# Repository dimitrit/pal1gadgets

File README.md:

# PAL1-GADGETS: A range of Gadgets for the PAL-1

The PAL-1 RIOT Expansion Module adds two bidirectional 8-bit digital input/output ports and a programmable interval timer to the PAL-1 system by means of a MOS6532 RAM-I/O-Timer (RIOT) IC.[^1]

This repository includes a number of `gadgets' that can be plugged in to the RIOT Expansion Module to provide specific functionality, including:

  * a [Real-Time Clock](../../tree/master/rtc)
  * a [Speech Processor](../../tree/master/speech)
  * an [Analog-to-Digital Converter](../../tree/master/adc)
  * an [IEC interface](../../tree/master/iec)

Refer to the relevant directories for details on each gadget.

Gadgets are plugged in to the PAL-1 RIOT Expansion Module using a [RIOT adapter](../../tree/master/adapter).

## Example code
Code examples are provided for most gadgets. These code examples use  `vasm6502_oldstyle` syntax[^2] and can be built using `make`.[^3]

## Acknowledgements
PAL-1 and the PAL-1 logo used with kind permission by Liu Ganning.

[^1]: Ganning, Liu, _‘RIOT EXPANSION’_, 2021 <http://pal.aibs.ws/assets/RIOT_expansion_manual.pdf> [accessed 26 January 2024].
[^2]: Barthelmann, Volker and Wille, Frank, `vasm assembler system' (2024), <http://sun.hasenbraten.de/vasm/daily/vasm.tar.gz> [accessed 27 March 2024].
[^3]: Free Software Foundation, `Make - GNU Project', <https://www.gnu.org/
software/make/> [accessed 27 March 2024].

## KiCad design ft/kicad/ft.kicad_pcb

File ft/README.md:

# PAL1-ft: An adapter for the fischertechnik Computing Interface

From the mid 1980s to the early 1990s fischertechnik released a number of construction sets that could be controlled by home computers.[^1] The connection between motors, sensors and the computer was by means of a dedicated Computing Interface.[^2] Different versions of the fischertechnik Computing Interface supported a range of platforms, including Amstrad, Apple, Atari and Commodore. In addition to these dedicated interfaces, fischertechnik also released universal interfaces. The fischertechnik Universal and CVK Computing Interfaces required adapters between the interface connector and target computer systems.

 PAL1-ft is a simple adapter that allows the fischertechnik Universal and CVK Computing Interfaces to be connected to the PAL-1 RIOT Expansion Module.[^3]

The PAL1-ft adapter implements mostly the same logical connections as the fischertechnik Commodore 64 adapter, with the exception of the analog data input:[^4]

| PAL1 RIOT | ft Interface | Description |
| :-------: | :----------: | :---------- |
| PB0       | LOAD_OUT     | Signal digital output |
| PB1       | LOAD_IN      | Signal digital input |
| PB2       | DATA_OUT     | Digital data output  stream |
| PB3       | CLOCK        | Data transfer clock |
| PB4       | TRIGGER_X    | Trigger analog input X |
| PB5       | TRIGGER_Y    | Trigger analog input Y |
| PB7       | DATA_IN<sup>*</sup>      | Digital data input stream |
| PA7       | COUNT_IN     | Analog data input pulses |

<sup>*</sup>The source of DATA_IN is determined by the Data Input Select Jumper. See documentation for details. 

Since the 6532 RIOT timer does not support a pulsed count down mode, the adapter instead routes the analog input to PA7, thereby enabling the use of the RIOT's edge sense interrupt feature. Alternatively, it is possible to measure analog inputs by calculating the time DATA_IN remains LOW after triggering an analog input. For this it is necessary to move the Data Input Select jumper to the CENTRONICS position.

[^1]: fischertechnik, _‘Robots, Automats and graphic units to build yourself’_, 1985, <https://docs.fischertechnikclub.nl/info2/1985.pdf> [accessed 1 September 2025]
[^2]: fischertechnik, _‘Computing Interface’_, N.D., <https://docs.fischertechnikclub.nl/computing/39484.pdf> [accessed 30 August 2025].
[^3]: Liu Ganning, _‘RIOT EXPANSION’_, 2021, <http://pal.aibs.ws/assets/RIOT_expansion_manual.pdf> [accessed 26 January 2024].
[^4]: R Trapp, _‘ft66843 Schematic’_, 2017, <https://ftcommunity.de/knowhow/computing/computing_interfaces/ft66843_schematic.pdf> [accessed 30 August 2025].

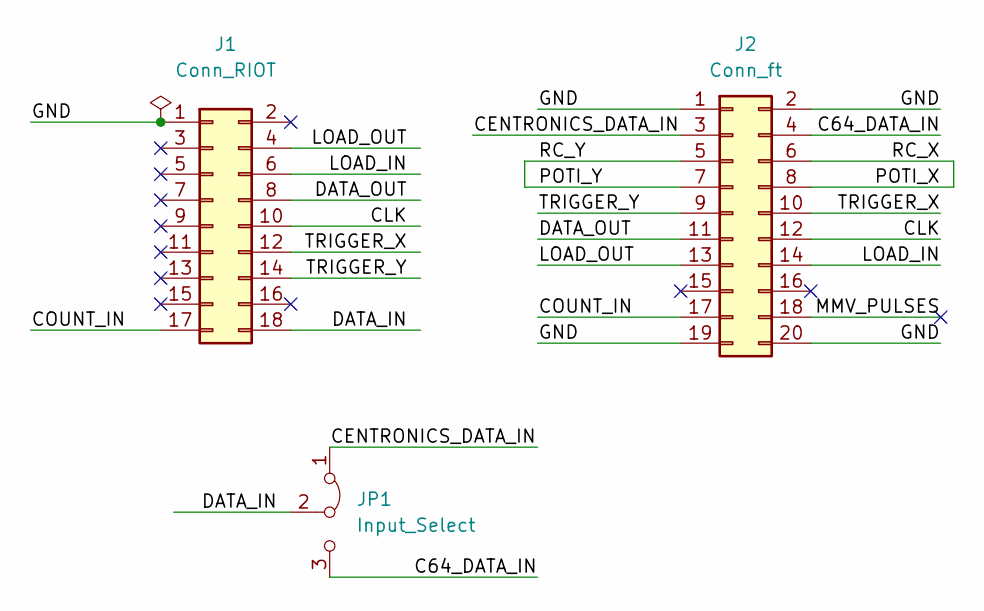
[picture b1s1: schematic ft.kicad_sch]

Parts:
J1: Conn_RIOT; PinSocket_2x09_P2.54mm_Horizontal
J2: Conn_ft; IDC-Header_2x10_P2.54mm_Horizontal
JP1: Input_Select; PinHeader_1x03_P2.54mm_Vertical

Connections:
/C64_DATA_IN: J2.4, JP1.3 (B)
/CENTRONICS_DATA_IN: J2.3, JP1.1 (A)
/CLK: J1.10, J2.12
/COUNT_IN: J1.17, J2.17
/DATA_IN: J1.18, JP1.2 (C)
/DATA_OUT: J1.8, J2.11
/GND: J1.1, J2.1, J2.2, J2.19, J2.20
/LOAD_IN: J1.6, J2.14
/LOAD_OUT: J1.4, J2.13
/MMV_PULSES: J2.18
/POTI_X: J2.6, J2.8
/POTI_Y: J2.5, J2.7
/TRIGGER_X: J1.12, J2.10
/TRIGGER_Y: J1.14, J2.9

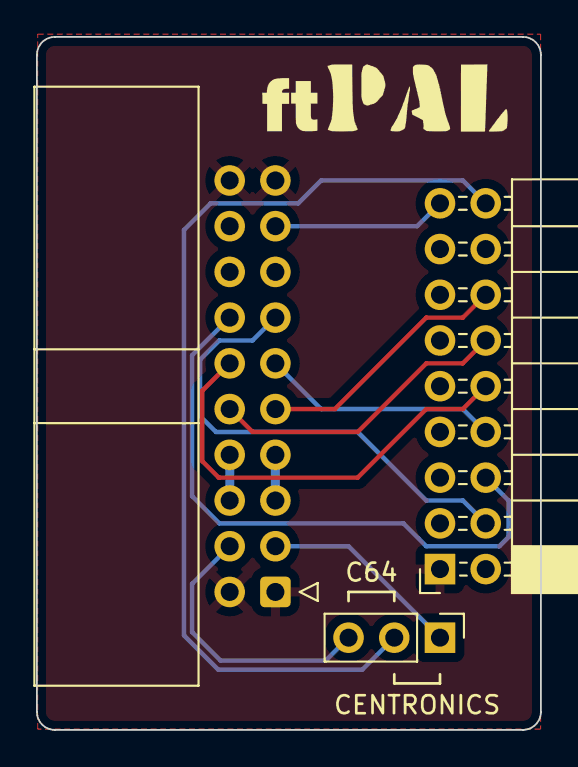
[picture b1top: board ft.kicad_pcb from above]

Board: 2 copper layers, 28.0 x 38.5 mm, 3 parts (0 on the bottom side), 13 nets.

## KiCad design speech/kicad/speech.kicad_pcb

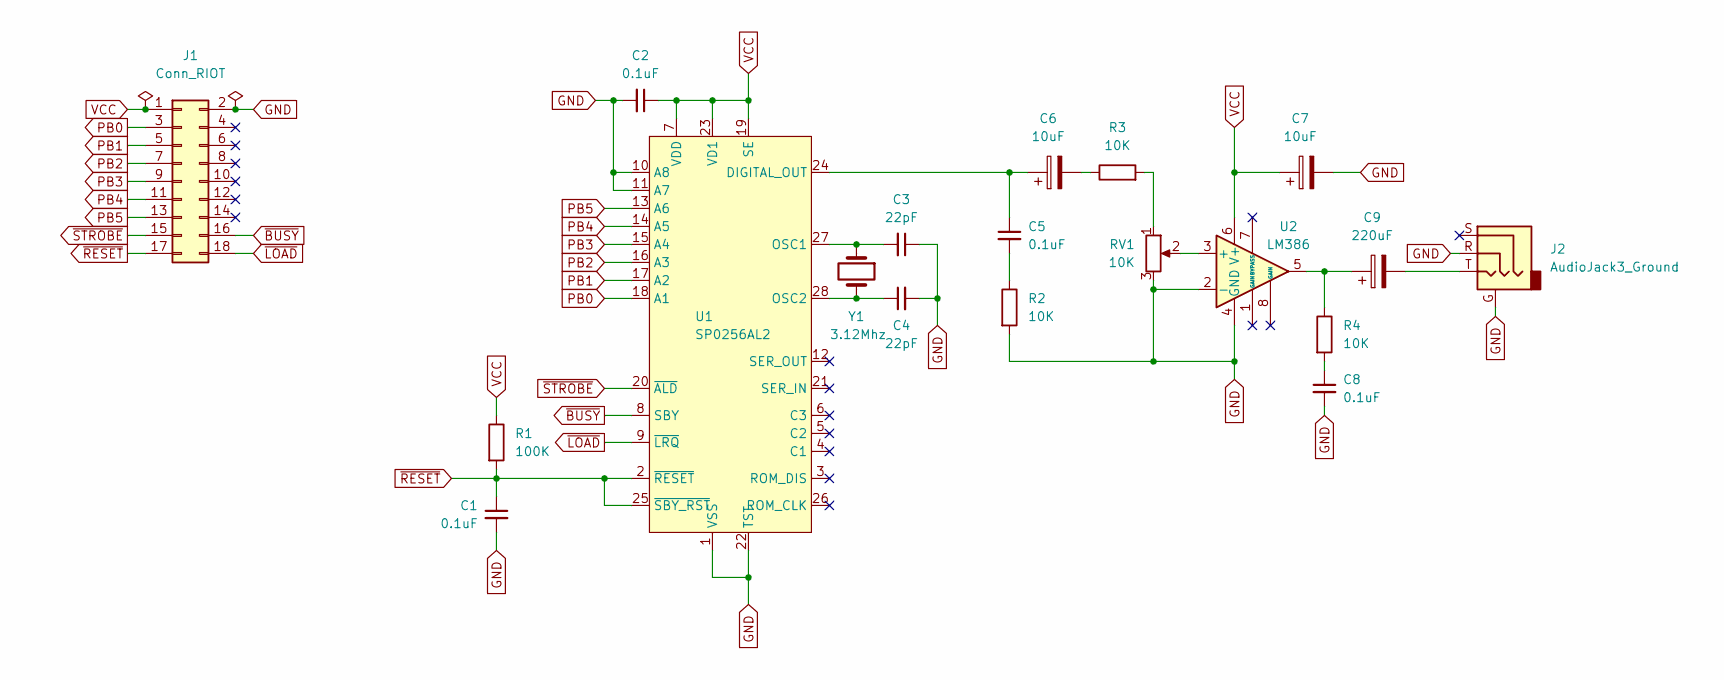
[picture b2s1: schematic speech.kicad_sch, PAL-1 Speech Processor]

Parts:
C1, C2, C5, C8: 0.1uF; C_Disc_D3.0mm_W1.6mm_P2.50mm
C3, C4: 22pF; C_Disc_D3.0mm_W1.6mm_P2.50mm
C6, C7: 10uF; CP_Radial_D5.0mm_P2.50mm
C9: 220uF; CP_Radial_D5.0mm_P2.50mm
J1: Conn_RIOT; PinHeader_2x09_P2.54mm_Vertical
J2: AudioJack3_Ground; Jack_3.5mm_4Pole_TRRS
R1: 100K; R_Axial_DIN0207_L6.3mm_D2.5mm_P7.62mm_Horizontal
R2, R3, R4: 10K; R_Axial_DIN0207_L6.3mm_D2.5mm_P7.62mm_Horizontal
RV1: 10K; Potentiometer_Runtron_RM065_Vertical
U1: SP0256AL2; DIP-28_W15.24mm
U2: LM386; DIP-8_W7.62mm
Y1: 3.12Mhz; Crystal_HC49-U_Vertical

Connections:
GND: C1.2, C2.2, C3.1, C4.2, C7.2, C8.2, J1.2, J2.G, J2.R, R2.2, RV1.3, U1.1 (VSS), U1.10 (A8), U1.11 (A7), U1.22 (TST), U2.2 (-), U2.4 (GND)
unnamed: C5.2, R2.1
unnamed: C6.2, R3.1
unnamed: C8.1, R4.2
unnamed: C9.1, R4.1, U2.5
unnamed: C9.2, J2.T
unnamed: R3.2, RV1.1
unnamed: C5.1, C6.1, U1.24 (DIGITAL_OUT)
unnamed: C3.2, U1.27 (OSC1), Y1.1
unnamed: C4.1, U1.28 (OSC2), Y1.2
unnamed: RV1.2, U2.3 (+)
PB0: J1.3, U1.18 (A1)
PB1: J1.5, U1.17 (A2)
PB2: J1.7, U1.16 (A3)
PB3: J1.9, U1.15 (A4)
PB4: J1.11, U1.14 (A5)
PB5: J1.13, U1.13 (A6)
VCC: C2.1, C7.1, J1.1, R1.1, U1.7 (VDD), U1.19 (SE), U1.23 (VD1), U2.6 (V+)
~BUSY: J1.16, U1.8 (SBY)
~LOAD: J1.18, U1.9 (~LRQ)
~RESET: C1.1, J1.17, R1.2, U1.2 (~RESET), U1.25 (~SBY_RST)
~STROBE: J1.15, U1.20 (~ALD)

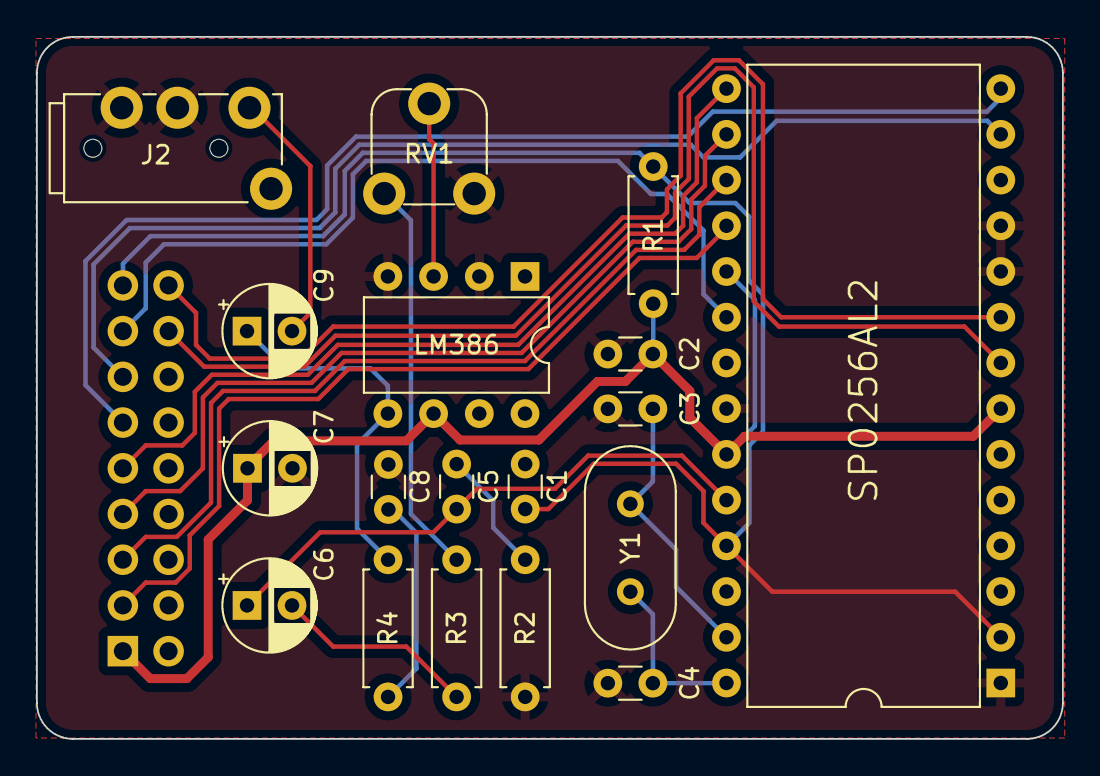
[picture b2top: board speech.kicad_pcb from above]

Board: 2 copper layers, 57.0 x 39.0 mm, 19 parts (1 on the bottom side), 22 nets.

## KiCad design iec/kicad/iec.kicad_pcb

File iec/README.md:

# PAL1-IEC: An IEC Adapter for the PAL-1

The PAL1-IEC gadget is an IEC/Serial adapter for the PAL-1 system intended to plug in to the PAL-1 RIOT Expansion Module.[^1]

The IEC gadget allows Commodore disk storage devices and printers to be connected to the PAL-1. The schematic is based on an original design by D McMurtrie.[^2]

[^1]: Liu Ganning, _‘RIOT EXPANSION’_, 2021 <http://pal.aibs.ws/assets/RIOT_expansion_manual.pdf> [accessed 26 January 2024].
[^2]: Dave McMurtrie, _'Implementing Commodore's IEC bus protocol on a KIM-1 single board computer'_, 2022 <https://www.youtube.com/watch?v=cK7mzGhBfHs> [accessed 12 March 2024]

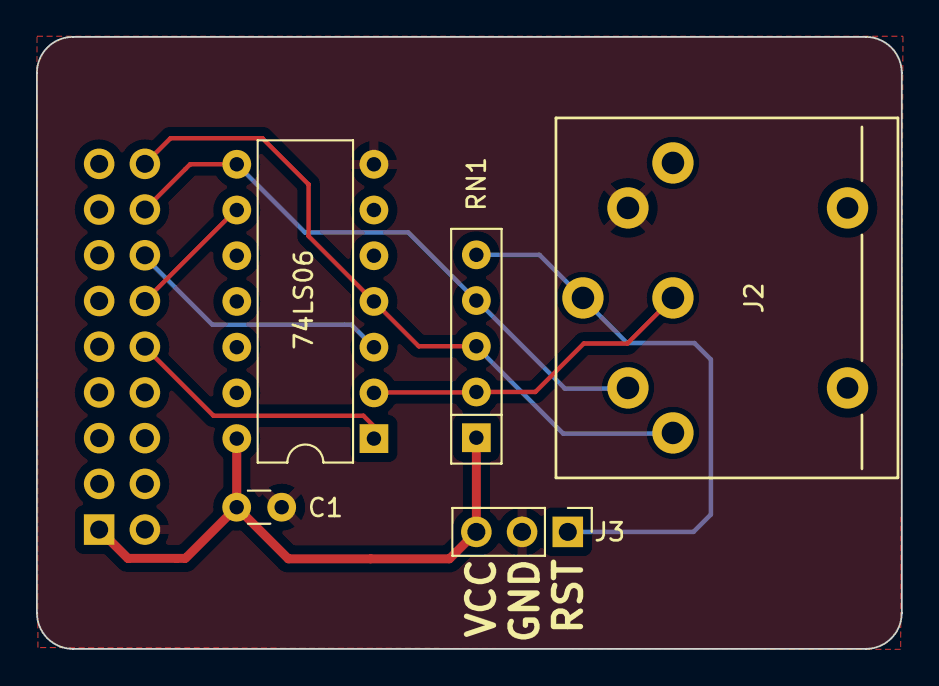
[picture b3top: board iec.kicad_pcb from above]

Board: 2 copper layers, 48.1 x 34.0 mm, 6 parts (1 on the bottom side), 9 nets.

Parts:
C1: 0.1uF; C_Disc_D3.0mm_W1.6mm_P2.50mm
J1: Conn_RIOT; PinHeader_2x09_P2.54mm_Vertical
J2: DIN-6
J3: Conn_Ext; PinHeader_1x03_P2.54mm_Vertical
RN1: 1K; R_Array_SIP5
U1: 74LS06; DIP-14_W7.62mm

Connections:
ATT: J2.3, RN1.2 (R1), U1.2
CLK: J1.16, J2.4, RN1.4 (R3), U1.8
DATA: J1.18, J2.5, RN1.3 (R2), U1.4
GND: C1.2, J1.2, J2.2, J3.2, U1.7 (GND)
PA3: J1.10, U1.1
PA4: J1.12, U1.9
PA5: J1.14, U1.3
VCC: C1.1, J1.1, J3.3, RN1.1 (common), U1.14 (VCC)
~RESET: J2.6, J3.1, RN1.5 (R4)

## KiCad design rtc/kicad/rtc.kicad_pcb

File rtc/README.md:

# PAL1-RTC: A Real Time Clock/Calendar for the PAL-1

PAL1-RTC is a real time clock/calendar for the PAL-1 system intended to plug in to the PAL-1 RIOT Expansion Module.[^1]

The clock/calendar provides seconds, minutes, hours, day, date, month, and year information. The end of the month date is automatically adjusted for months with fewer than 31 days, including corrections for leap year. The clock operates in either the 24-hour or 12-hour format with AM/PM indicator. In addition, 96 bytes of NV RAM are provided for data storage. Refer to the DS1305 datasheet for details.[^2]

[^1]: Liu Ganning, _‘RIOT EXPANSION’_, 2021 <http://pal.aibs.ws/assets/RIOT_expansion_manual.pdf> [accessed 26 January 2024].
[^2]: Maxim Integrated Products, _‘DS1305
Serial Alarm Real-Time Clock’_, 2015 <https://www.analog.com/media/en/technical-documentation/data-sheets/DS1305.pdf> [accessed 26 January 2024].

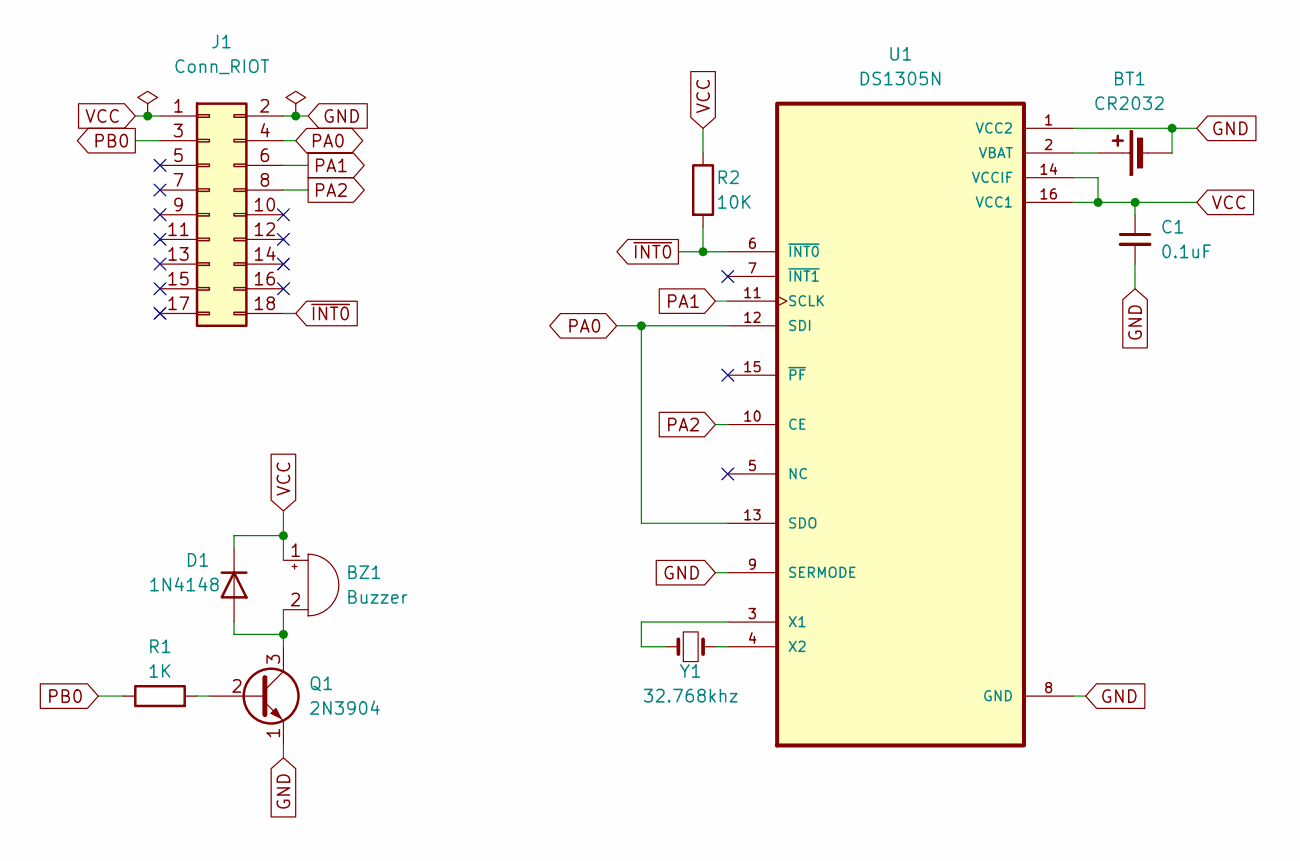
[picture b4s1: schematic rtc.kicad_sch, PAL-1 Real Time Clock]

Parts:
BT1: CR2032; CH7410-2032
BZ1: Buzzer; Buzzer_12x9.5RM7.6
C1: 0.1uF; C_Disc_D3.0mm_W1.6mm_P2.50mm
D1: 1N4148; D_DO-35_SOD27_P7.62mm_Horizontal
J1: Conn_RIOT; PinHeader_2x09_P2.54mm_Vertical
Q1: 2N3904; TO-92_Inline_Wide
R1: 1K; R_Axial_DIN0207_L6.3mm_D2.5mm_P7.62mm_Horizontal
R2: 10K; R_Axial_DIN0207_L6.3mm_D2.5mm_P7.62mm_Horizontal
U1: DS1305N; DIP-16_W7.62mm
Y1: 32.768khz; Crystal_C26-LF_D2.1mm_L6.5mm_Horizontal

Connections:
GND: BT1.2 (-), C1.2, J1.2, Q1.1 (E), U1.1 (VCC2), U1.8 (GND), U1.9 (SERMODE)
unnamed: BT1.1 (+), U1.2 (VBAT)
unnamed: BZ1.2 (+), D1.2 (A), Q1.3 (C)
unnamed: Q1.2 (B), R1.2
unnamed: U1.3 (X1), Y1.1
unnamed: U1.4 (X2), Y1.2
PA0: J1.4, U1.12 (SDI), U1.13 (SDO)
PA1: J1.6, U1.11 (SCLK)
PA2: J1.8, U1.10 (CE)
PB0: J1.3, R1.1
VCC: BZ1.1 (-), C1.1, D1.1 (K), J1.1, R2.1, U1.14 (VCCIF), U1.16 (VCC1)
~INT0: J1.18, R2.2, U1.6 (~INT0)

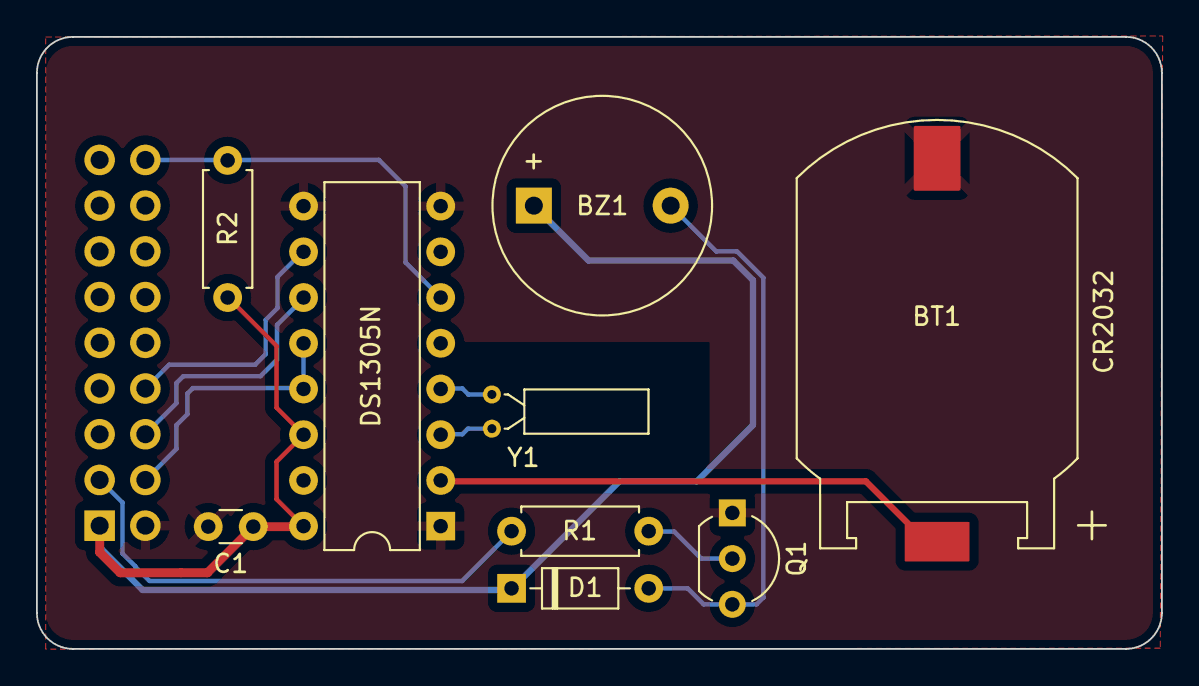
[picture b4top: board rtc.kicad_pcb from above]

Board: 2 copper layers, 62.5 x 34.0 mm, 10 parts (1 on the bottom side), 12 nets.

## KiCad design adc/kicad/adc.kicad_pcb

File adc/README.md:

# PAL1-ADC: An Analog to Digital Converter for the PAL-1

The PAL1-ADC is an Analog-to-Digital Converter for the PAL-1 system intended to plug in to the PAL-1 RIOT Expansion Module[^1].

The analog-to-digital converter enables high throughput data capture (up to 200 kSPS) via an 8-bit 'bus'. A small on-board prototype area facilitates experimentation. Refer to the AD7819 datasheet[^2] for details.

## Acknowledgement

The `wozfp.a65` and `bcdfp.a65` source files are from Jeff Tranter's github repository and have been modified for `vasm6502_oldstyle` syntax.[^3]

[^1]: Liu Ganning, _‘RIOT EXPANSION’_, 2021 <http://pal.aibs.ws/assets/RIOT_expansion_manual.pdf> [accessed 26 January 2024].
[^2]: Analog Devices, _‘AD7819, 2.7 V to 5.5 V, 200 kSPS
8-Bit Sampling ADC’_, 2000 <https://www.analog.com/media/en/technical-documentation/data-sheets/AD7819.pdf> [accessed 29 February 2024].
[^3]: Jeff Tranter, _‘README’_, N.D., <https://github.com/jefftranter/6502/tree/master/asm/wozfp> [accessed 8 April 2024].

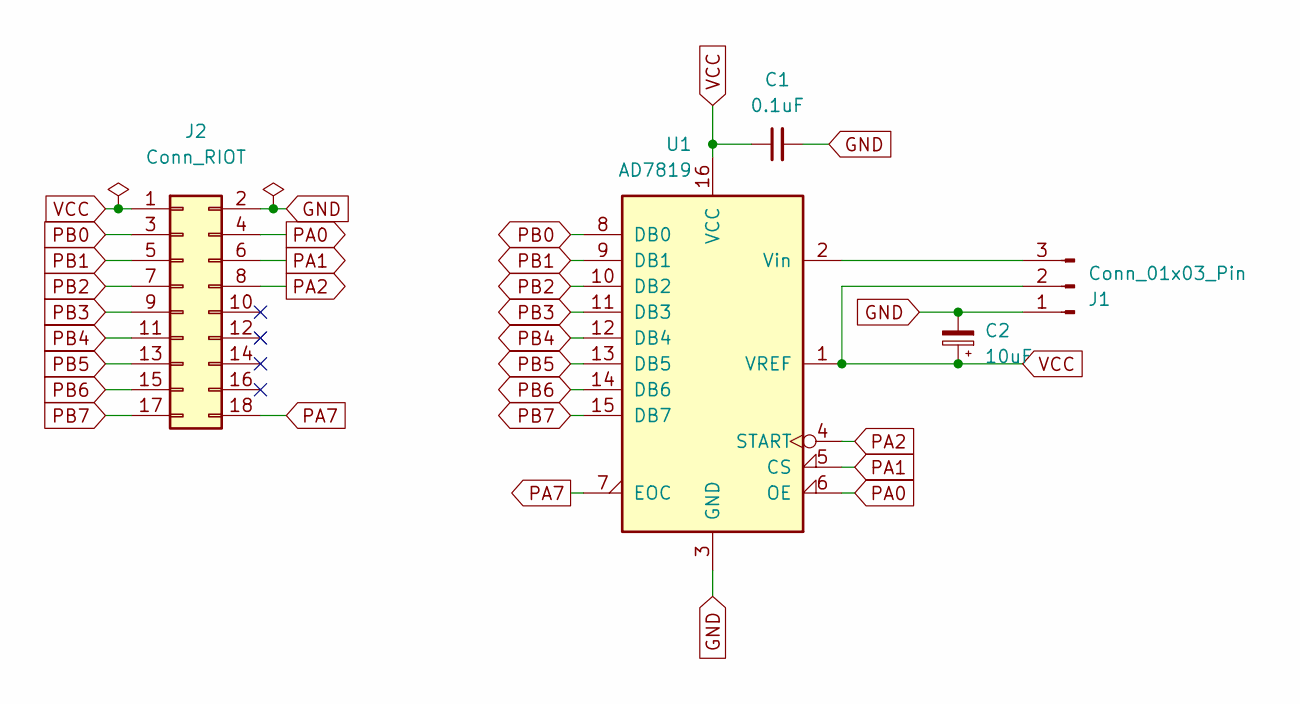
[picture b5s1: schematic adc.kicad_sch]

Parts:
C1: 0.1uF; C_Disc_D3.0mm_W1.6mm_P2.50mm
C2: 10uF; CP_Radial_D5.0mm_P2.50mm
J1: Conn_01x03_Pin; PinHeader_1x03_P2.54mm_Horizontal
J2: Conn_RIOT; PinHeader_2x09_P2.54mm_Vertical
U1: AD7819; DIP-16_W7.62mm

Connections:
GND: C1.2, C2.2, J1.1, J2.2, U1.3 (GND)
unnamed: J1.3, U1.2 (Vin)
PA0: J2.4, U1.6 (OE)
PA1: J2.6, U1.5 (CS)
PA2: J2.8, U1.4 (START)
PA7: J2.18, U1.7 (EOC)
PB0: J2.3, U1.8 (DB0)
PB1: J2.5, U1.9 (DB1)
PB2: J2.7, U1.10 (DB2)
PB3: J2.9, U1.11 (DB3)
PB4: J2.11, U1.12 (DB4)
PB5: J2.13, U1.13 (DB5)
PB6: J2.15, U1.14 (DB6)
PB7: J2.17, U1.15 (DB7)
VCC: C1.1, C2.1, J1.2, J2.1, U1.1 (VREF), U1.16 (VCC)

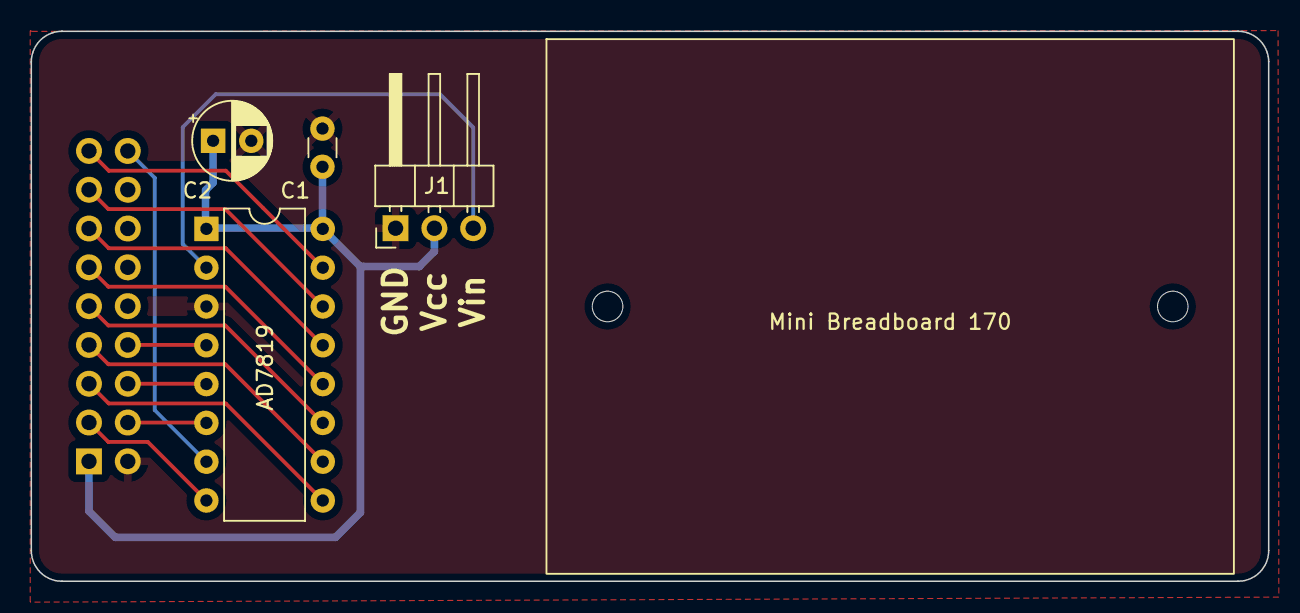
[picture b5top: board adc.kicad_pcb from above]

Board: 2 copper layers, 81.0 x 36.0 mm, 6 parts (1 on the bottom side), 15 nets.

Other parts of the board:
BB1: Mini Breadboard 170

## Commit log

2024-02-07 Add sample rtc code
2024-02-07 Add readme
2024-03-10 Exclude gerber directories
2024-03-10 Add RTC kicad designs
2024-03-10 Add RTC gadget render
2024-03-10 Add image
2024-03-11 Add adapter
2024-03-11 Add adapter readme
2024-03-11 Add LICENSE
2024-03-12 Add IEC gadget
2024-03-12 Fix styling issue
2024-03-12 Add A/D converter
2024-03-12 Add render to readme
2024-03-12 Fix typo
2024-03-15 Change transistor pads to make soldering easier
2024-03-23 Add acknowledgement
2024-03-23 Moves images to figures
2024-03-23 Update image paths
2024-03-23 Add links
2024-03-23 Update links
2024-03-23 Add link to adapter
2024-03-25 Expose VCC and GND via pins for SD2IEC devices
2024-03-26 Add buzzer example
2024-04-25 Update ADC docs
2024-04-25 Initial implementation of speech gadget
2024-07-21 Update schematic and board layout
2024-07-21 Update documentation
2024-07-21 Add General Instrument documentation
2024-07-21 Update main README
2024-07-21 Add code examples
2024-07-21 Add Makefile
2024-07-31 Add code example
2024-09-01 Add SNES controller demo
2024-09-01 Add kicad files
2024-09-01 Add images
2025-08-30 Initial version of the ft interface
2025-08-30 Add ftPAL render
2025-08-30 Add ftPAL Readme
2025-08-30 Fix formatting issue
2025-08-30 Add clarification
2025-08-30 Improve documentation
2025-08-30 Change ft interface connector to IDC type
2025-08-31 Add link to ft66843 schematic
2025-09-01 Update silkscreen
2025-09-01 Add ft sample programs
2025-09-05 Update logo
2025-09-06 Initial port of C64 ft driver
2025-09-06 Reformat code
2025-09-09 Reverse engineer VIC20 driver
2025-09-09 Add futher comments
2025-09-09 Add missing value
2025-09-11 Add DATA_IN selection jumper
2025-09-12 Update examples
2025-09-13 Refactor labels
2025-10-03 Update simple digital example
2025-10-05 Provide addtional details
2025-10-20 Add prototype ir receiver
2025-10-23 Initial NEC version
2025-10-25 Add left and right shifts
